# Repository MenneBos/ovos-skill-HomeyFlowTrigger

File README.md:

# **OVOS-Skill-HomeyFlowTrigger**

The `ovos-skill-HomeyFlowTrigger` repository is an OpenVoiceOS (OVOS) skill designed to integrate with the Homey Pro smart home ecosystem. It allows users to trigger Homey flows using voice commands, manage flow mappings, and interact with Homey through a web interface and MQTT communication.

---

## **Features**

1. **Homey API Integration**:
   - Communicates with Homey Pro using the Homey API v3 to retrieve and trigger flows.
   - Supports secure interaction with Homey using API keys.

2. **Homey Flow Management**:
   - Dynamically fetches Homey flows and maps them to custom voice commands (utterances).
   - Allows users to edit, delete, or add new flows via a web interface.

3. **Web Interface**:
   - A simple HTML-based interface for managing `flow_mappings.json`.
   - Users can view, edit, and save flow mappings, as well as add new flows by fetching them from Homey.

4. **MQTT Communication**:
   - Uses MQTT to communicate between the web interface and the Python skill.
   - Topics include:
     - `request_flow_mappings`: Fetch the current flow mappings.
     - `send_flow_mappings`: Send the flow mappings to the web interface.
     - `save_flow_mappings`: Save updated flow mappings from the web interface.
     - `request_flows`: Fetch available flows from Homey.
     - `send_flows`: Send filtered flows from Homey to the web interface.
     - To-Do command to receive 

5. **Fuzzy Matching**:
   - Uses fuzzy logic to match voice commands to flows, even with slight deviations in utterances.

6. **Dynamic Intent Updates**:
   - Automatically updates `.intent` files and retrain OVOS Padatious when flow mappings are modified.

7. ***Persistent User Data**
   - The skill now stores user-specific configuration and flow mappings in the directory `~/.config/ovos-skill-homeyflowtrigger/`.
   - This ensures that your `config.json` and `flow_mappings.json` are preserved across skill upgrades and reinstalls.
---

## **How It Works**

1. **Voice Command Execution**:
   - A user speaks a command (e.g., "presence in office").
   - The skill matches the command to a flow using fuzzy logic and triggers the corresponding flow via the Homey API.

2. **Flow Management via Web Interface**:
   - Users can view and edit `flow_mappings.json` in a user-friendly format.
   - New flows can be fetched from Homey and added to the mappings.

3. **MQTT Communication**:
   - The web interface publishes and subscribes to MQTT topics to interact with the Python skill.
   - The Python skill processes the requests and communicates with Homey via Node.js subprocesses.

---

## **Installation Guide**

### **1. Prerequisites**
- **Python**: Ensure Python 3.8+ is installed.
- **Node.js**: Install Node.js for running Homey API scripts.
- **MQTT Broker**: Set up an MQTT broker (e.g., Mosquitto) with secure TLS configuration.

### **2. Clone the Repository**
```bash
git clone https://github.com/your-repo/ovos-skill-HomeyFlowTrigger.git
cd ovos-skill-HomeyFlowTrigger
```

### **3. Install Python Dependencies**
Create a virtual environment and install the required Python libraries:
```bash
python -m venv venv
source venv/bin/activate  # On Windows: venv\Scripts\activate
pip install -r requirements.txt
```

### **4. Install Node.js Dependencies**
Navigate to the Node.js scripts directory and install dependencies:
```bash
cd nodejs
npm install homey-api
```
- The Node.js scripts (`get_flow.js`, `start_flow.js`) now read `config.json` from the user config directory:
  - `~/.config/ovos-skill-homeyflowtrigger/config.json`
- Ensure this file exists and is correctly configured before running the scripts.

### **5. Configure Homey API**
- Generate an API key for Homey Pro via the Homey app or web interface.
- Update the `get_flow.js` and `start_flow.js` scripts with your Homey API key and IP address.

### **6. Configure MQTT Broker**
- Install and configure Mosquitto or another MQTT broker.
- Set up secure communication with TLS and user authentication.
- Update the Python skill and web interface with the broker's address, port, username, and password.

### **7. Run the Skill**
Start the skill in your OVOS environment:
```bash
systemctl --user restart ovos.service
```

### **8. Launch the Web Interface**
- Open the `index.html` file in a browser.
- Enter the brokers' host ip address
- Use the buttons to fetch, edit, and save flow mappings.

---

## **Connecting to the Broker and Homey**

### **1. Broker Configuration**
- Ensure the MQTT broker is running and accessible.
- Update the Python skill and web interface with the broker's connection details.

### **2. Homey API Configuration**
- Ensure you have the Homey Pro 2023
- Create a API access key on the homey
- Ensure the Homey Pro device is reachable on the network.
- Update the Node.js scripts with the correct API key and IP address.

### **3. Testing the Connection**
- Use the web interface to publish a `request_flow_mappings` topic.
- Verify that the Python skill responds with the `send_flow_mappings` topic.

---

## **Example Workflow**

1. **Fetch Flow Mappings**:
   - Click the "Fetch Flow Mappings" button in the web interface.
   - The Python skill publishes the current `flow_mappings.json` to the web interface.

2. **Edit Flow Mappings**:
   - Modify the flow mappings in the web interface (e.g., add or edit utterances).
   - Save the changes, which publishes the updated mappings to the broker.

3. **Add a New Flow**:
   - Click the "Request Flows" button to fetch available flows from Homey.
   - Select a flow and add it to the local mappings.

4. **Trigger a Flow**:
   - Speak a command that (almost) matches the intent/command given in the website.
   - The skill triggers the corresponding flow via the Homey API.

---

## **Topics Overview**

### **Published Topics**
1. `request_flow_mappings`: Request the current flow mappings.
2. `save_flow_mappings`: Save updated flow mappings.
3. `request_flows`: Request available flows from Homey.

### **Subscribed Topics**
1. `send_flow_mappings`: Receive the current flow mappings.
2. `saved_flow_mappings`: Receive a confirmation of saved mappings.
3. `send_flows`: Receive filtered flows from Homey.

---

## **Block Diagam**

```mermaid
  info
```

```mermaid
graph TD;
    OVOS_Core <--> Hivemind-Listener; 
    Hivemind-Listener  <--> Hivemind_Satellite_raspZero_2;
    OVOS_Core <--> OVOS_MQTT_Client;
    OVOS_MQTT_Client <--> MQTT_Broker;
    Laptop <--> HTML;
    HTML <--> User_MQTT_Client; 
    User_MQTT_Client <--> MQTT_Broker;
    Homey_Pro_2023 <--> Local_v3_API;
    Local_v3_API <--> GetFlow_TriggerFlow;
    GetFlow_TriggerFlow <--> OVOS_Core;
```
This repository provides a powerful and flexible way to control Homey flows using OVOS, enabling seamless integration between voice commands and smart home automation.

---
**Persistent User Data**

- The skill now stores user-specific configuration and flow mappings in the directory `~/.config/ovos-skill-homeyflowtrigger/`.
- This ensures that your `config.json` and `flow_mappings.json` are preserved across skill upgrades and reinstalls.
---

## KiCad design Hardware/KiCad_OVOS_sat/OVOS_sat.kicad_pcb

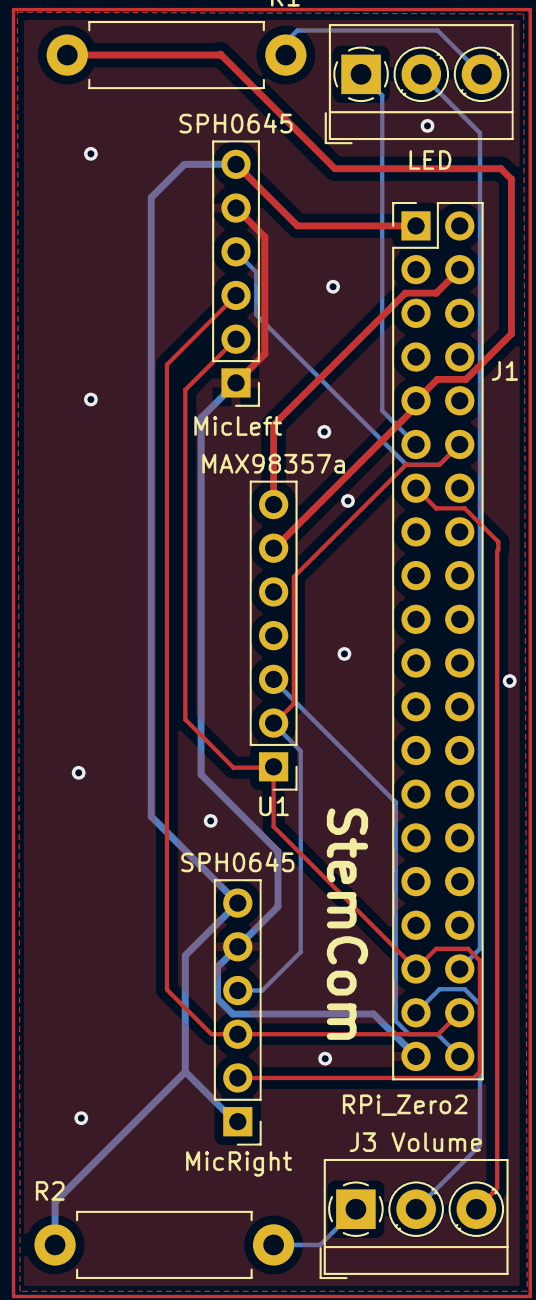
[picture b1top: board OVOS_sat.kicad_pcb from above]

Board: 2 copper layers, 8 parts (0 on the bottom side), 14 nets.

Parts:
J1: RPi_Zero2; PinHeader_2x20_P2.54mm_Vertical
J3 Volume: Volume; TerminalBlock_MetzConnect_Type059_RT06303HBWC_1x03_P3.50mm_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
LED: LED; TerminalBlock_MetzConnect_Type059_RT06303HBWC_1x03_P3.50mm_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
MicLeft: SPH0645; PinHeader_1x06_P2.54mm_Vertical
MicRight: SPH0645; PinHeader_1x06_P2.54mm_Vertical
R1, R2: R_Small; R_Axial_DIN0411_L9.9mm_D3.6mm_P12.70mm_Horizontal
U1: MAX98357a; PinHeader_1x07_P2.54mm_Vertical

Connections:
unnamed: J1.1 (3V3), MicLeft.6 (VDD), MicRight.1 (SEL), MicRight.6 (VDD), R2.2
unnamed: J1.4 (5V), U1.7 (Vin)
unnamed: J1.9 (GND), R1.2, U1.6 (GND)
unnamed: J1.11 (GPIO17), LED.1
unnamed: J1.12 (GPIO18/PWM0), MicLeft.4 (BCLK), MicRight.4 (BCLK), U1.2 (Bclk)
unnamed: J1.13 (GPIO27), J3 Volume.3
unnamed: J1.35 (GPIO19/MISO1), MicLeft.2 (LRCLK), MicRight.2 (LRCLK), U1.1 (LRC)
unnamed: J1.36 (GPIO16), LED.2
unnamed: J1.37 (GPIO26), J3 Volume.2
unnamed: J1.38 (GPIO20/MOSI1), MicLeft.3 (DOUT), MicRight.3 (DOUT)
unnamed: J1.39 (GND), MicLeft.1 (SEL), MicLeft.5 (GND), MicRight.5 (GND)
unnamed: J1.40 (GPIO21/SCLK1), U1.3 (Din)
unnamed: LED.3, R1.1
unnamed: J3 Volume.1, R2.1

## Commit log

2025-05-03 first
2025-05-03 Refactor flow triggering logic and update intent vocabulary; remove unused vocab files
2025-05-03 Update package_data in setup.py to specify resource files directly
2025-05-03 Refactor project structure: remove unnecessary files and restore versioning
2025-05-03 Fix version file path in get_version function
2025-05-03 top top
2025-05-03 Fix URL in setup.py and update resource directories in find_resource_files function
2025-05-03 Restore HomeyFlowSkill implementation and intent file
2025-05-03 Fix log message formatting in handle_start_flow method and add flow_mappings.json file
2025-05-03 Add json import to __init__.py for JSON handling
2025-05-03 Update path for Node.js script in handle_start_flow method
2025-05-03 Fix flow ID logging and update flow trigger ID in Node.js script
2025-05-03 Improve error handling and logging messages in flow trigger scripts
2025-05-03 Refactor flow mapping initialization and improve error handling in handle_start_flow method
2025-05-03 Refactor flow mappings to include detailed object structure for flow IDs and names
2025-05-04 Use dynamic flow ID from command line argument in triggerFlow method
2025-05-05 Refactor HomeyFlowSkill and add flow mappings; implement favorite flow retrieval in Node.js
2025-05-11 Refactor flow mappings and remove unused code
    - Updated flow_mappings.json to include "Kantoor Check out" and "Kantoor Check in" flows with their respective IDs and sentences.
    - Deleted the get_favorite_flow.js file as it was no longer needed.
    - Modified setup.py to include "shared" in resource_base_dirs and removed "cryptography" from install_requires.
    - Added CA certificate, private key, and server certificate files for secure connections.
    - Created index.html and index_unsecure.html for the Flow Mappings Manager with MQTT functionality.
    - Added server certificate request and private key files for secure server setup.
2025-05-11 Update MQTT connection port to 9001 for WebSocket
2025-05-11 Improve MQTT message handling by stripping whitespace from payload and adding default empty dictionary for empty payloads
2025-05-11 Update Homey API token in get_flow.js for local API connection
2025-05-11 Add get_flow.js to implement Homey API flow retrieval with search functionality
2025-05-11 Update paths for Node.js scripts in flow request handling
2025-05-16 Refactor flow handling in HTML and improve flow retrieval in Node.js
2025-05-16 Enhance flow selection by converting flow object to array and adding alert for no flows found
2025-05-16 Enhance flow selection UI by displaying available flows in a list with add buttons
2025-05-16 Enhance flow handling by loading flow mappings from JSON and searching for utterances in flow sentences
2025-05-16 Update flow mappings and intents to include additional sentences for flow recognition
2025-05-17 Add user alert for flow mapping request and restore intent file
2025-05-17 Add user alert for saving flow mappings
2025-05-17 Clear and recreate intent files based on flow mappings
2025-05-17 Sanitize flow names in payload when saving flow mappings and update intent files accordingly
2025-05-17 Normalize flow names in mappings and enhance logging for flow execution
2025-05-17 Sanitize flow names in handle_start_flow method and enhance logging for flow execution
2025-05-17 Enhance logging in handle_start_flow method to include received message data
2025-05-17 Enhance handle_start_flow method with improved logging and flow name extraction
2025-05-17 Enhance handle_start_flow method to improve utterance extraction and logging of flow name
2025-05-17 Refactor handle_start_flow method to improve utterance extraction and logging, and update on_settings_changed and log_level properties for dynamic settings handling
2025-05-17 Refactor flow mappings to replace 'flow_id' with 'id' for consistency in data structure
2025-05-17 Enhance fuzzy matching in handle_start_flow method for improved flow name extraction and logging; add difflib to requirements
2025-05-17 Remove difflib from install_requires in setup.py
2025-05-17 Remove obsolete files and update README for improved clarity on HomeyFlowTrigger integration and usage
2025-05-17 Refactor configuration loading in get_flow and start_flow scripts; update .gitignore and requirements.txt for improved clarity and consistency
2025-05-17 Remove obsolete certificate and key files for improved security and maintenance
2025-05-18 Add error logging for missing broker_url and info logging for successful config loading
2025-05-18 Add logging for missing broker_url and info for successful loading
2025-05-18 Refactor broker_url extraction and add logging for its value
2025-05-18 Add login and password fields to HiveMQ connection; improve config loading error handling
2025-05-18 Add logging for the path to start_Flow.js in HomeyFlowSkill
2025-05-18 Refactor MQTT message publishing to use Paho.MQTT.Message for request and save operations
2025-05-18 Refactor MQTT message handling to use a unified message processing function
2025-05-18 Refactor MQTT message handling: uncomment on_message method and add subscriptions for flow mappings
2025-05-18 Fix method signature for MQTT message handling in HomeyFlowSkill
2025-05-18 Add logging for MQTT topic and payload in _on_mqtt_message method
2025-05-18 Subscribe to additional MQTT topics for flow mappings and update logging format in _on_mqtt_message method
2025-05-18 Update flow request handling to use the correct script path and improve subprocess execution
2025-05-18 Refactor flow request handling to use the correct Node.js script and improve subprocess execution
2025-05-28 Remove package-lock.json to clean up unused dependencies
2025-05-28 Update .gitignore to include nodejs/package-lock.json and modify logging in get_flow.js for clarity
2025-05-30 Increase input field width in index_hiveMQ.html and change log level message to info in __init__.py
2025-06-01 Remove obsolete HTML files and update index_hiveMQ and index_unsecure to enhance MQTT client functionality with device prefix support and improved UI elements.
2025-06-14 upodate
2025-06-14 Add language detection and intent handling for HomeyFlowSkill; create test_homey.intent files for both English and Dutch locales.
2025-06-14 Add HomeyFlowSkill implementation with MQTT support and intent handling
2025-06-14 Refactor get_default_lang function to simplify configuration file handling
2025-06-14 Remove event registration for homey_flow_trigger and simplify config loading log message
2025-06-14 Fix string interpolation in MQTT message logging
2025-06-14 Add method to save configuration to config.json with error handling
2025-06-15 Add existing device name functionality and enhance MQTT message handling
2025-06-19 Stop tracking flow_mappings.json
2025-06-19 Implement config saving method and update flow mappings
2025-06-20 Enhance language detection logging and improve user feedback for flow actions
2025-06-20 Update configuration loading to use user-specific directory
2025-06-20 Refactor flow start responses for improved clarity and consistency; update user feedback messages in both Python and JavaScript files.
2025-06-28 Remove obsolete HTML and Python test files for MQTT flow mappings
2025-06-28 Fix configuration path for HomeyFlowSkill to use underscores instead of hyphens
2025-06-28 Fix configuration path in start_flow.js to use underscores instead of hyphens
2025-06-30 Implement code changes to enhance functionality and improve performance
2025-06-30 Comment out runtime requirements in HomeyFlowSkill to prevent unnecessary loading conditions
2025-07-04 Update .gitignore, backlog.md, HTML files, and get_flow.js for improved configuration handling and added default broker settings
2025-07-10 Refactor HomeyFlowSkill to enhance settings handling and add dynamic log level retrieval; introduce default broker configuration files.
2025-07-10 Add language detection and logging in HomeyFlowSkill initialization
2025-07-10 Refactor HomeyFlowSkill to improve settings handling; reintroduce language detection and dynamic log level retrieval.
2025-07-10 Refactor HomeyFlowSkill to streamline configuration loading and enhance device information extraction.
2025-07-10 Refactor HomeyFlowSkill by commenting out the __init__ method and removing unnecessary whitespace in the initialize method.
2025-07-10 Refactor HomeyFlowSkill to simplify language detection logic and ensure default intent directory is set for Dutch language.
2025-07-10 Refactor HomeyFlowSkill to implement language detection and set default intent directory for Dutch and English languages.
2025-07-16 Remove 'Bash scrips' directory from Git tracking
2025-07-16 cleaned up
2025-07-16 add additional files
2025-12-12 minimal code
2025-12-27 docker
